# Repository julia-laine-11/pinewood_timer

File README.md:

# pinewood_timer
Timer system for a pinewood derby track. My grandma asked me to help her make one since her boy scout troop's track does not have one. I hope that I can make these more affordable so that her troop and other troops can get accurate timers that dont cost an arm and a leg.

*so whats in here?*
### [Hardware:](https://github.com/julia-laine-11/pinewood_timer/tree/main/Hardware)
* display_15_in
    - schematic
    - pcb
    - holds all the 7-segment displays and sensor receivers at the end of the track

* mainboard
    - schematic
    - pcb
    - holds the brains for the system
    - also where the power cable goes

### [Software:](https://github.com/julia-laine-11/pinewood_timer/blob/main/Software/code.md)
  - readme
* [Program](https://github.com/julia-laine-11/pinewood_timer/tree/main/Software/code/pinewood_program)
  - platformio project

### Overview
#### Overall Requirements
- easy operation -> plug and play
- 4 lanes
- time to the thousandths
- displays time in each lane
- displays placement in each lane
- cost less than $100-$120
    - 

##### Requirements per each lane
- start sensor - same trigger for all lanes
- stop sensor - seperate per each lane
- time display - 4 seven seg displays
- placement display - 1 larger seven seg display

##### Sensors
- Start sensor triggered by lever release
  - Microswitch is easy to install and get output from
  - I have to wait and see what my grandfather builds as the start mechanism
- Stop sensor - IR LED and IR Receiver
  - Sits in the middle of the groove the cars ride on underneath the finish line
  - Since it will likely be in a gym, the IR receiver should point down for less interference from the large lamps
  - A comparator or the STM ADC can be used if the voltage doesnt drop to an amount the STM recognizes as 0

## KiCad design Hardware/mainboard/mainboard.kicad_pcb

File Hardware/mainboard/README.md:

## mainboard

This board will be placed in a central location on the track. It connects to the power, reset button, start sensors, display at the end, and end sensors. A usb-c power supply will power it.

#### Current Board

9/30/25 - today i soldered the LED on. i got scared it wasnt working, but it turns out it was just a blue LED and therefore needed a smaller resistor. Then i plugged it in and i thought hte JTAG was backwards, but it turns out the decoup capacitors I placed are not in face decoupling and just capacitors. so i removed them and added a wire around them. im having issues connecting to the board. 

i got access to the board files from ece362, so i plan on comparing my layout to theirs to see what i did wrong. im disappointed but i think i can fix it (hopefully)

#### Current schematic
8/7/25 - fixed little silkscreen words. fixed DRC violations

### Old:

8/5/25 - i actually routed stuff today wohoo. i also added the design rules because i forgot to do that

not too much changed about the schematic:

i just added this for the start switch because i forgot about it

8/3/25 - added connectors and sheets

7/27/25 - organized and fixed power

7/26/25 - changed stm. added jtag. added usb for power. edited 3v3 supply. current schematic messy but its still in the works

Unfinished schematic

missing:
- connectors
- power in
- jtag
- usb - ttl

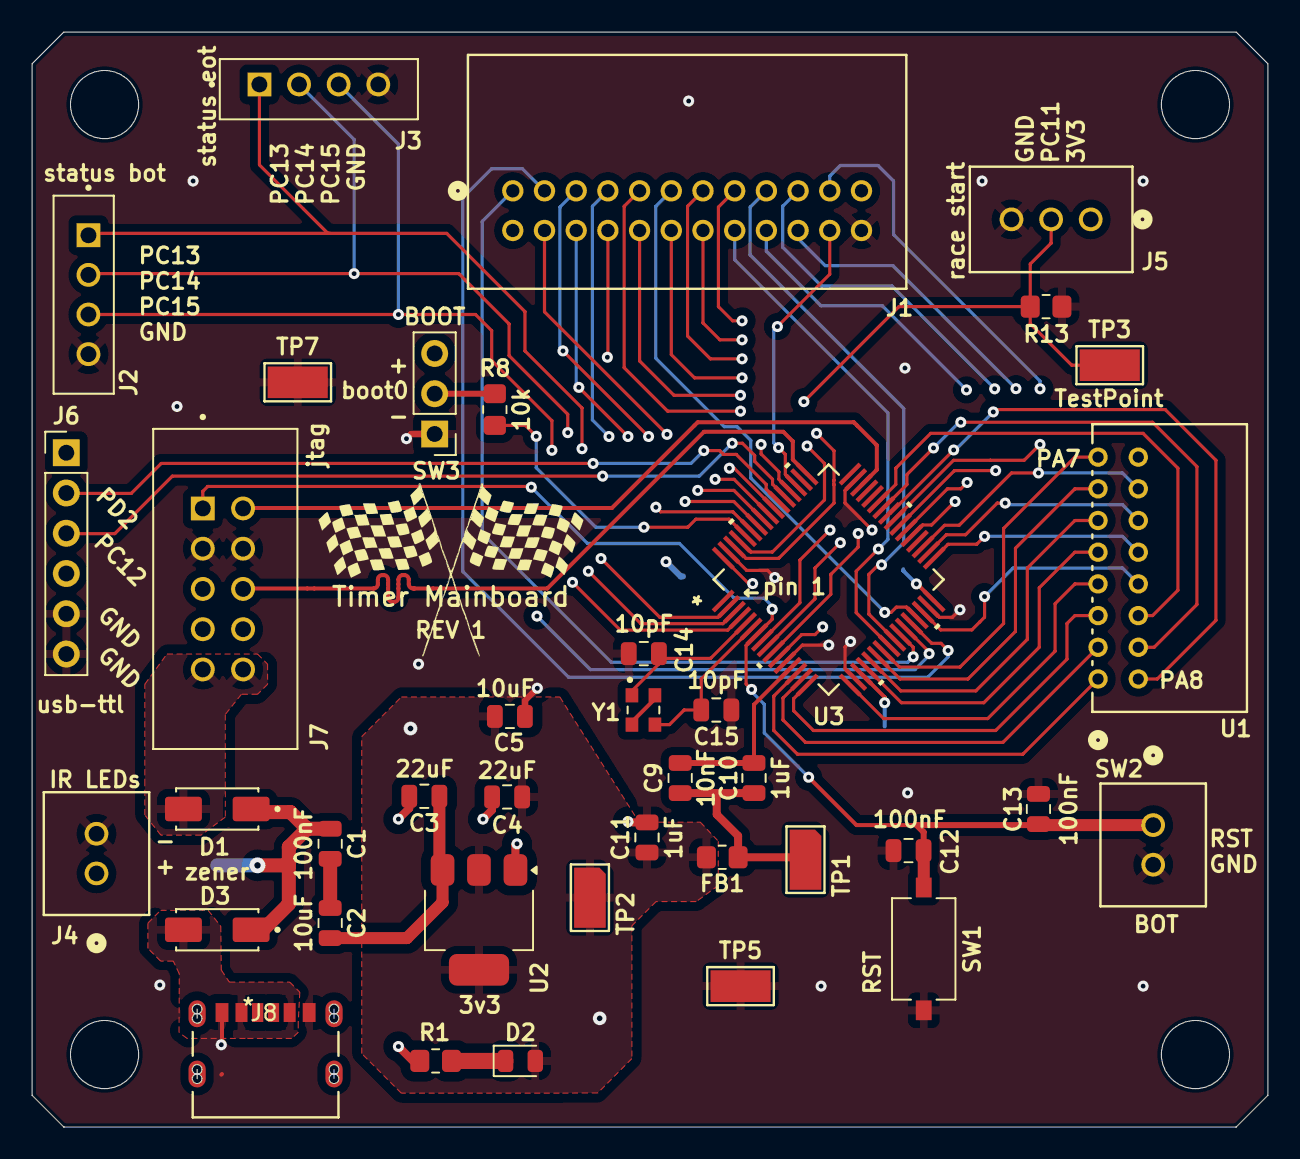
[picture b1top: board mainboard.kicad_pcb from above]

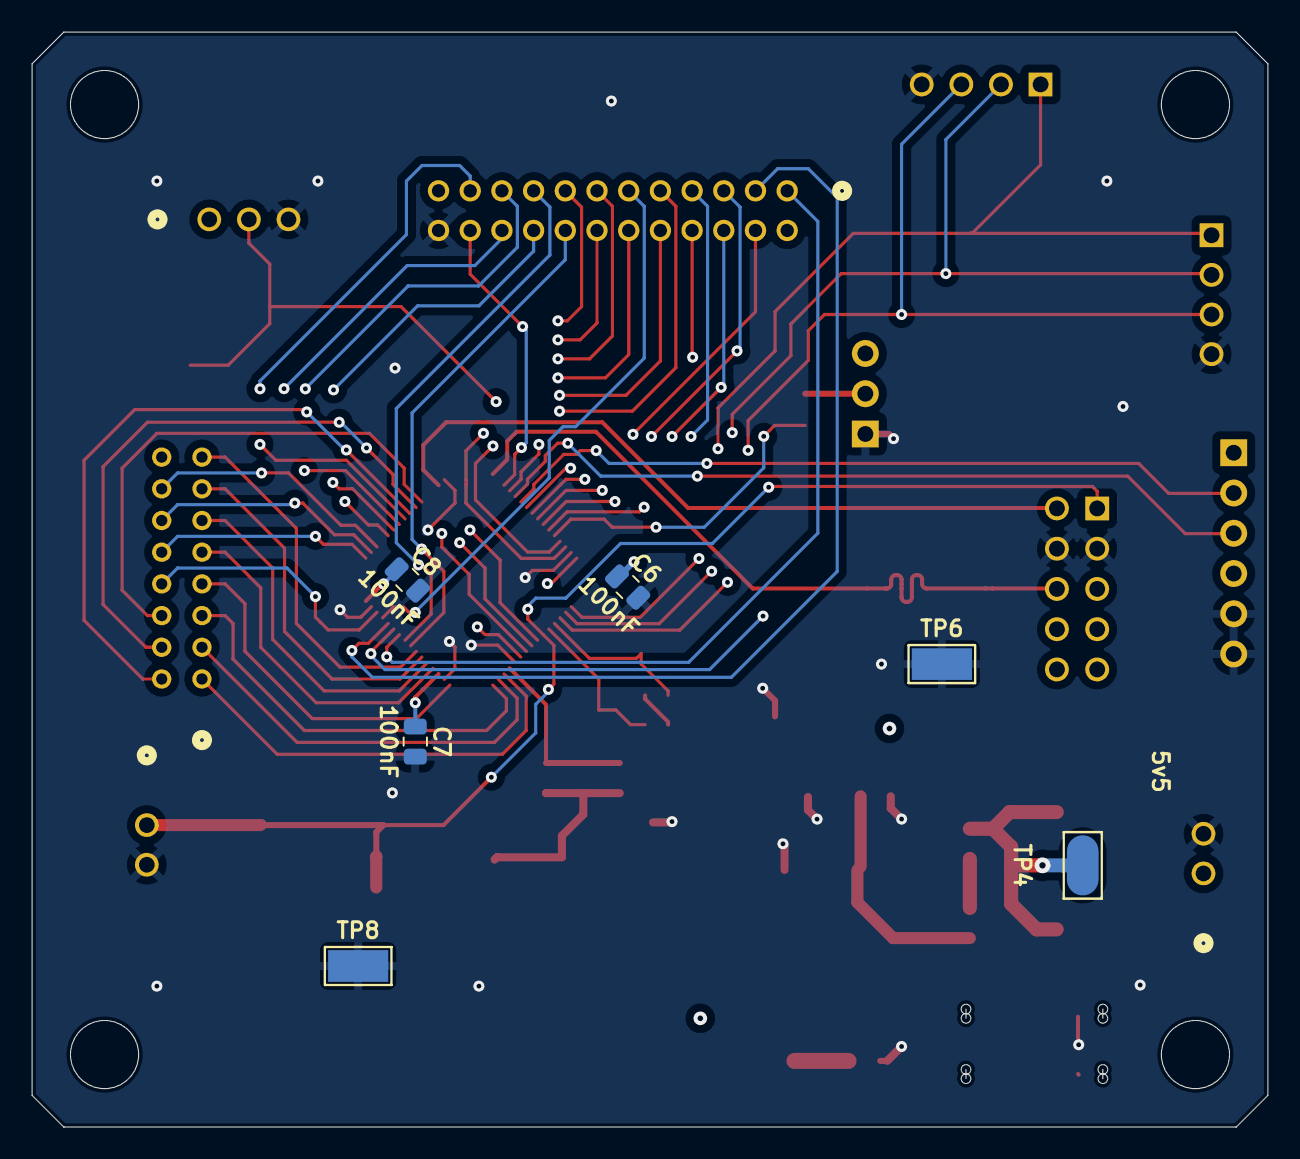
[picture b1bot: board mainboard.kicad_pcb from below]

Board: 4 copper layers, 78.0 x 69.1 mm, 49 parts (6 on the bottom side), 61 nets.

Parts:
C1, C6, C7, C8, C12, C13: 100nF; C_0805_2012Metric
C2, C5: 10uF; C_0805_2012Metric
C3, C4: 22uF; C_0805_2012Metric
C9: 10nF; C_0805_2012Metric
C10, C11: 1uF; C_0805_2012Metric
C14, C15: 10pF; C_0805_2012Metric
D1, D3: zener; DIOM5226X240N
D2: LED; D_0805_2012Metric
FB1: FerriteBead; R_0805_2012Metric_Pad1.20x1.40mm_HandSolder
H1, H2, H3, H4: MountingHole; MountingHole_4.3mm_M4_DIN965
J1: 559592430; CONN24_559592430_MOL
J2: status bot; 1x04_jst
J3: status eot; 1x04_jst
J4: B02B-XASK-1LFSN; 1X02_JST
J5: race start; 1X03_JST
J6: usb-ttl; PinHeader_1x06_P2.54mm_Vertical
J7: jtag; SULLINS_SBH11-PBPC-D05-ST-BK
J8: KUSBX-SMT-CS-6-BTR; 2171750001_MOL
R1: 1k5; R_0805_2012Metric_Pad1.20x1.40mm_HandSolder
R8: 10k; R_0805_2012Metric_Pad1.20x1.40mm_HandSolder
R13: R_US; R_0805_2012Metric_Pad1.20x1.40mm_HandSolder
SW1: ON-BOARD; SW_Tactile_SPST_NO_Straight_CK_PTS636Sx25SMTRLFS
SW2: BOT; CONN_B02B-XASK-1LFSN_JST
SW3: BOOT; PinHeader_1x03_P2.54mm_Vertical
TP1, TP2, TP3, TP4, TP5, TP6, TP7, TP8: TestPoint; TestPoint_Keystone_5019_Minature
U1: S16B-PHDSSLFSN; S16B-PHDSSLFSN_JST
U2: AMS1117-3.3; SOT-223-3_TabPin2
U3: STM32F091RCTx; STM32F091RCT6-M
Y1: Crystal_GND24; OSC_ECS-2520S25-250-FN-TR

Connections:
+3.3V: C4.1, C5.1, C6.1, C7.1, C8.1, C11.1, D2.2 (A), FB1.2, J1.23, J4.1, J5.1, SW3.3 (C), TP2.1, U2.2 (VO), U3.19 (VDD), U3.32 (VDD), U3.64 (VDD)
+3.3VA: C9.1, C10.1, FB1.1, TP1.1
/programming/3V3 REG DECOUP: C1.2, C2.1
/programming/3v3_reg_in: C2.2, C3.1, U2.3 (VI)
/programming/5v5_in_jtag: D1.2, J7.9, J7.10
/programming/5v5_post_diode: C1.1, D1.1, D3.1, TP4.1
/programming/5v5_usb: D3.2, J8.A9 (VBUS), J8.B9 (VBUS)
/programming/PWR_LED_CATHODE: D2.1 (K), R1.2
/stm/BOOT0: R8.2, U3.60 (PF11)
/stm/HSE_IN: C14.1, U3.5 (PF0), Y1.1
/stm/HSE_OUT: C15.1, U3.6 (PF1), Y1.3
/stm/SW_BOOT0: R8.1, SW3.2 (B)
GND: C3.2, C4.2, C5.2, C6.2, C7.2, C8.2, C11.2, C12.2, C13.2, C14.2, C15.2, J1.24, J2.4, J3.4, J4.2, J5.3, J6.5, J6.6, J7.3, J7.4, J8.A12 (GND), J8.B12 (GND), R1.1, R13.2, SW1.2 (B), SW2.2 (B), SW3.1 (A), TP5.1, TP6.1, TP7.1, TP8.1, U2.1 (GND), U3.12 (VSSA), U3.18 (VSS), U3.31 (VSS), U3.47 (VSS), U3.63 (VSS)
unnamed: C9.2, C10.2, U3.13 (VDDA)
unnamed: Y1.2, Y1.4
PA0: U1.1, U3.14 (PA0)
PA1: U1.2, U3.15 (PA1)
PA2: U1.3, U3.16 (PA2)
PA3: U1.4, U3.17 (PA3)
PA4: U1.5, U3.20 (PA4)
PA5: U1.6, U3.21 (PA5)
PA6: U1.7, U3.22 (PA6)
PA7: U1.8, U3.23 (PA7)
PA8: U1.9, U3.41 (PA8)
PA9: U1.10, U3.42 (PA9)
PA10: U1.11, U3.43 (PA10)
PB0: J1.1, U3.26 (PB0)
PB1: J1.2, U3.27 (PB1)
PB2: J1.3, U3.28 (PB2)
PB3: J1.4, U3.55 (PB3)
PB4: J1.5, U3.56 (PB4)
PB5: J1.6, U3.57 (PB5)
PB6: J1.7, U3.58 (PB6)
PB7: J1.8, U3.59 (PB7)
PB8: J1.9, U3.61 (PB8)
PB9: J1.10, U3.62 (PB9)
PB10: J1.11, U3.29 (PB10)
PB11: U1.12, U3.30 (PB11)
PB12: U1.13, U3.33 (PB12)
PB13: U1.14, U3.34 (PB13)
PB14: U1.15, U3.35 (PB14)
PC0: J1.12, U3.8 (PC0)
PC1: J1.13, U3.9 (PC1)
PC2: J1.14, U3.10 (PC2)
PC3: J1.15, U3.11 (PC3)
PC4: J1.16, U3.24 (PC4)
PC5: J1.17, U3.25 (PC5)
PC6: J1.18, U3.37 (PC6)
PC7: J1.19, U3.38 (PC7)
PC8: J1.20, U3.39 (PC8)
PC9: J1.21, U3.40 (PC9)
PC10: J1.22, U3.51 (PC10)
PC11: J5.2, R13.1, TP3.1, U3.52 (PC11)
PC12: J6.3, U3.53 (PC12)
PC13: J2.1, J3.1, U3.2 (PC13)
PC14: J2.2, J3.2, U3.3 (PC14)
PC15: J2.3, J3.3, U3.4 (PC15)
PD2: J6.2, U3.54 (PD2)
RST: C12.1, C13.1, J7.1, SW1.1 (A), SW2.1 (A), U3.7 (NRST)
SWCLK: J7.6, U3.49 (PA14)
SWDIO: J7.2, U3.46 (PA13)

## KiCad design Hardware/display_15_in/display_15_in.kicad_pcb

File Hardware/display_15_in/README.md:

## display_15_in
This was originally going to be a few seperate boards. I thought it would be easier and cheaper to make. 

It turns out to be cheaper to do it this way since the price of printing 3-4 boards per track and the price of 1 big one is the same. Also, with multiple boards you have to buy connectors and this 1 large board needs way less than 4 small ones.

This board connects to the main board with 1 8x2 connector and 1 12x2 connector.

### Parts
- LTS-3401LG - single 7-seg displays
- 4x TDCR1050M - quad 7-seg displays
- 20x PN2907A - cathode select bjt
- 20x 150 Ohm - mux to bjt
- 16x 47 Ohm - driver to display
- 2x 74HC138 - mux
- 2x TLC59211 - driver

#### pictures

>size comparison of digits 

#### schematics

#### PCB

Updated:

- still needs
  - power and ground traces
  - drill holes for mounting
  - test points

All traces routed (for now)

#### Log

7/12/25 - moved all of the components needed over to one project

7/13/25 - worked out connections between sheets and found connectors for mainboard. began layout (no traces)

7/19/25 - laying more traces and revising old ones. i am starting to hate the connector but i must use it

7/20/25 - sorted out the connector from hell. well, i at least made it better. i also discovered the "distribute evenly" and "align" functions

7/25/25 - finished traces, added test points

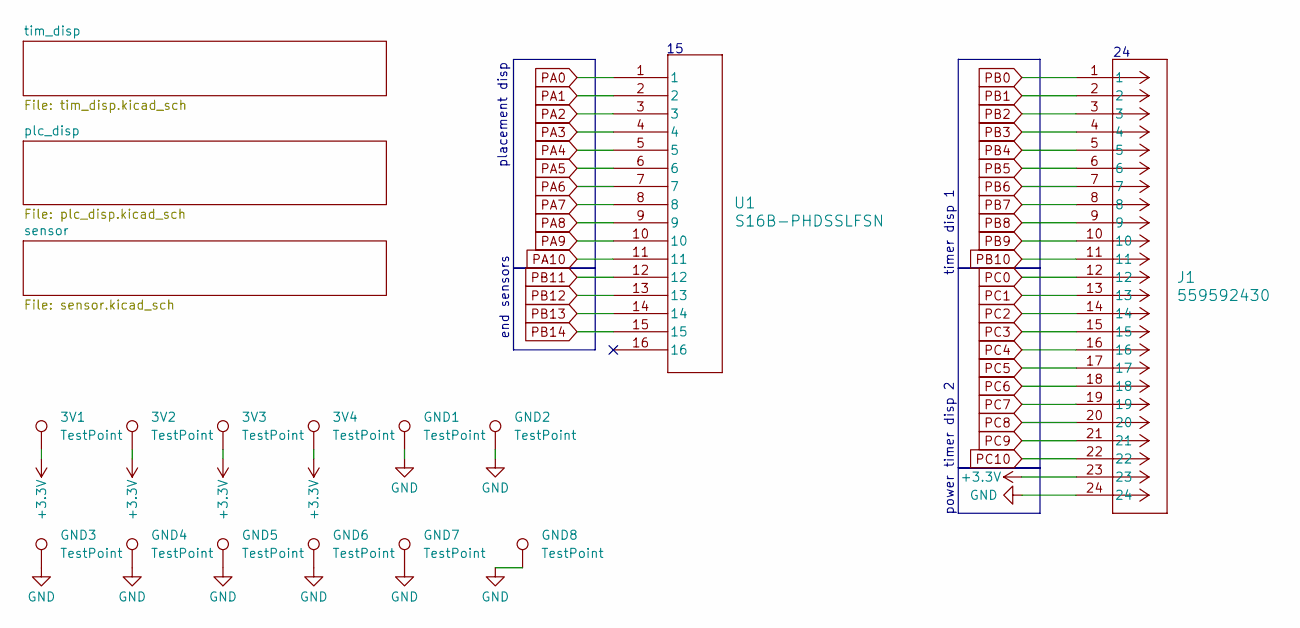
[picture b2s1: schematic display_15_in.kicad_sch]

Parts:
3V1, 3V2, 3V3, 3V4: TestPoint; TestPoint_Keystone_5019_Minature
GND1, GND2, GND3, GND4, GND5, GND6, GND7, GND8: TestPoint; TestPoint_Keystone_5019_Minature
J1: 559592430; CONN24_559592430_MOL
U1: S16B-PHDSSLFSN; S16B-PHDSSLFSN_JST

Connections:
+3.3V: 3V1.1, 3V2.1, 3V3.1, 3V4.1, J1.23; also elsewhere on the board
GND: GND1.1, GND2.1, GND3.1, GND4.1, GND5.1, GND6.1, GND7.1, GND8.1, J1.24; also elsewhere on the board
PA0: U1.1; also elsewhere on the board
PA1: U1.2; also elsewhere on the board
PA2: U1.3; also elsewhere on the board
PA3: U1.4; also elsewhere on the board
PA4: U1.5; also elsewhere on the board
PA5: U1.6; also elsewhere on the board
PA6: U1.7; also elsewhere on the board
PA7: U1.8; also elsewhere on the board
PA8: U1.9; also elsewhere on the board
PA9: U1.10; also elsewhere on the board
PA10: U1.11; also elsewhere on the board
PB0: J1.1; also elsewhere on the board
PB1: J1.2; also elsewhere on the board
PB2: J1.3; also elsewhere on the board
PB3: J1.4; also elsewhere on the board
PB4: J1.5; also elsewhere on the board
PB5: J1.6; also elsewhere on the board
PB6: J1.7; also elsewhere on the board
PB7: J1.8; also elsewhere on the board
PB8: J1.9; also elsewhere on the board
PB9: J1.10; also elsewhere on the board
PB10: J1.11; also elsewhere on the board
PC0: J1.12; also elsewhere on the board
PC1: J1.13; also elsewhere on the board
PC2: J1.14; also elsewhere on the board
PC3: J1.15; also elsewhere on the board
PC4: J1.16; also elsewhere on the board
PC5: J1.17; also elsewhere on the board
PC6: J1.18; also elsewhere on the board
PC7: J1.19; also elsewhere on the board
PC8: J1.20; also elsewhere on the board
PC9: J1.21; also elsewhere on the board
PC10: J1.22; also elsewhere on the board

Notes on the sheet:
power
timer disp 2
end sensors
placement disp
timer disp 1

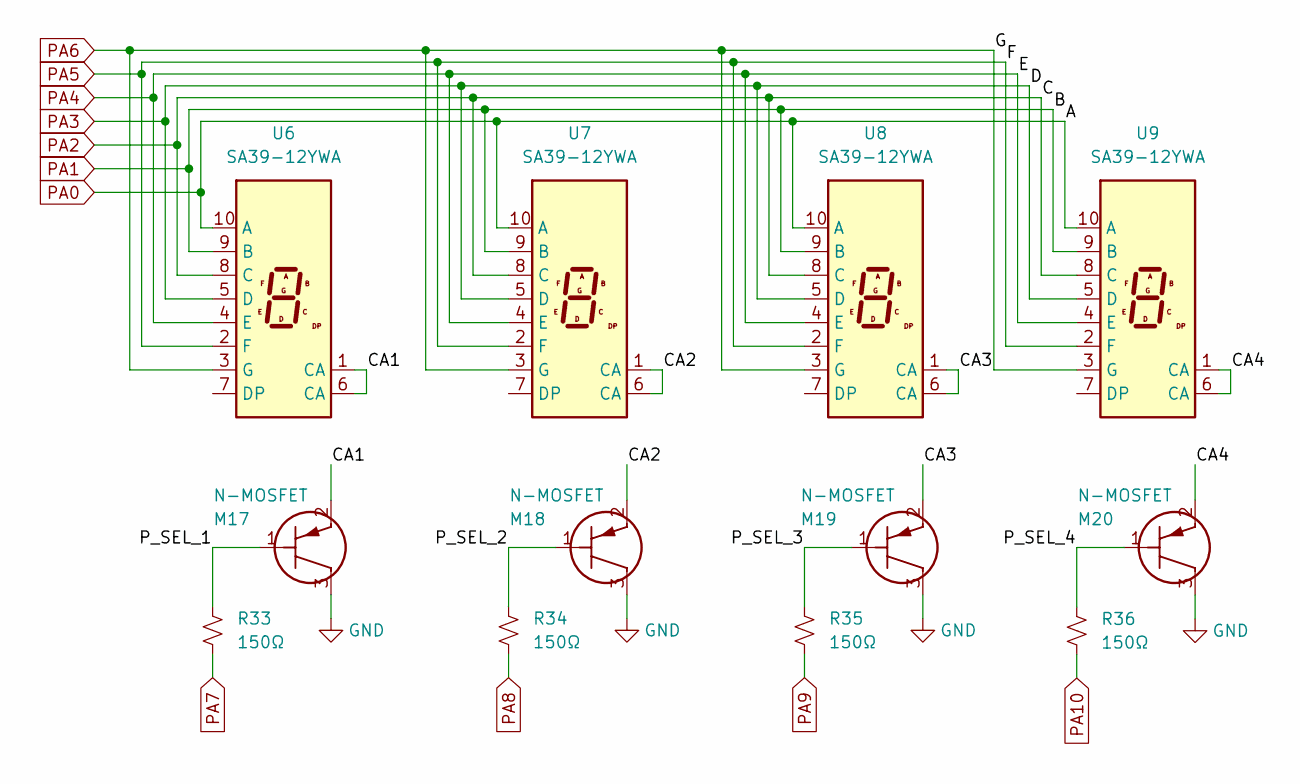
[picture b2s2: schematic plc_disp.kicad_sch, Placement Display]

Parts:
M17, M18, M19, M20: N-MOSFET; TO-236AB_SOT23_NEX
R33, R34, R35, R36: 150Ω; R_0805_2012Metric
U6, U7, U8, U9: SA39-12YWA; LDS-AA14RI

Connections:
/plc_disp/CA1: M17.2, U6.1 (CA), U6.6 (CA)
/plc_disp/CA2: M18.2, U7.1 (CA), U7.6 (CA)
/plc_disp/CA3: M19.2, U8.1 (CA), U8.6 (CA)
/plc_disp/CA4: M20.2, U9.1 (CA), U9.6 (CA)
/plc_disp/P_SEL_1: M17.1, R33.1
/plc_disp/P_SEL_2: M18.1, R34.1
/plc_disp/P_SEL_3: M19.1, R35.1
/plc_disp/P_SEL_4: M20.1, R36.1
GND: M17.3, M18.3, M19.3, M20.3; also elsewhere on the board
PA0: U6.10 (A), U7.10 (A), U8.10 (A), U9.10 (A); also elsewhere on the board
PA1: U6.9 (B), U7.9 (B), U8.9 (B), U9.9 (B); also elsewhere on the board
PA2: U6.8 (C), U7.8 (C), U8.8 (C), U9.8 (C); also elsewhere on the board
PA3: U6.5 (D), U7.5 (D), U8.5 (D), U9.5 (D); also elsewhere on the board
PA4: U6.4 (E), U7.4 (E), U8.4 (E), U9.4 (E); also elsewhere on the board
PA5: U6.2 (F), U7.2 (F), U8.2 (F), U9.2 (F); also elsewhere on the board
PA6: U6.3 (G), U7.3 (G), U8.3 (G), U9.3 (G); also elsewhere on the board
PA7: R33.2; also elsewhere on the board
PA8: R34.2; also elsewhere on the board
PA9: R35.2; also elsewhere on the board
PA10: R36.2; also elsewhere on the board

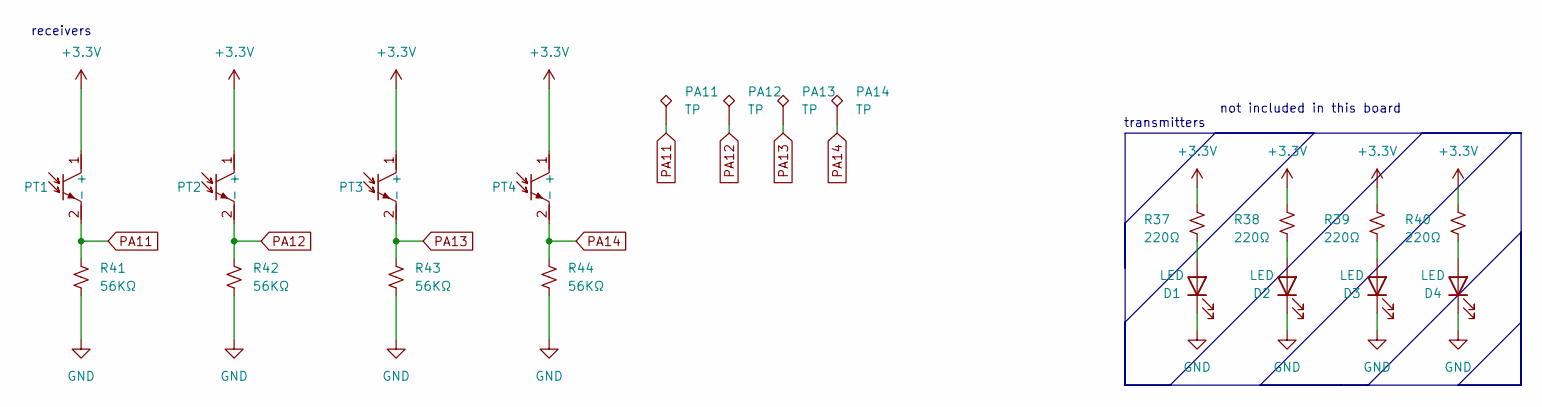
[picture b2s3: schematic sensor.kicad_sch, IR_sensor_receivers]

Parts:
D1, D2, D3, D4: LED; LED_D5.0mm
PA11, PA12, PA13, PA14: TP; TestPoint_Keystone_5019_Minature
PT1, PT2, PT3, PT4: LED_D5.0mm
R37, R38, R39, R40: 220Ω; R_0805_2012Metric
R41, R42, R43, R44: 56KΩ; R_0805_2012Metric

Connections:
+3.3V: PT1.1 (+), PT2.1 (+), PT3.1 (+), PT4.1 (+), R37.1, R38.1, R39.1, R40.1; also elsewhere on the board
GND: D1.1 (K), D2.1 (K), D3.1 (K), D4.1 (K), R41.2, R42.2, R43.2, R44.2; also elsewhere on the board
unnamed: D1.2 (A), R37.2
unnamed: D2.2 (A), R38.2
unnamed: D3.2 (A), R39.2
unnamed: D4.2 (A), R40.2

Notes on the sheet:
receivers
transmitters
not included in this board

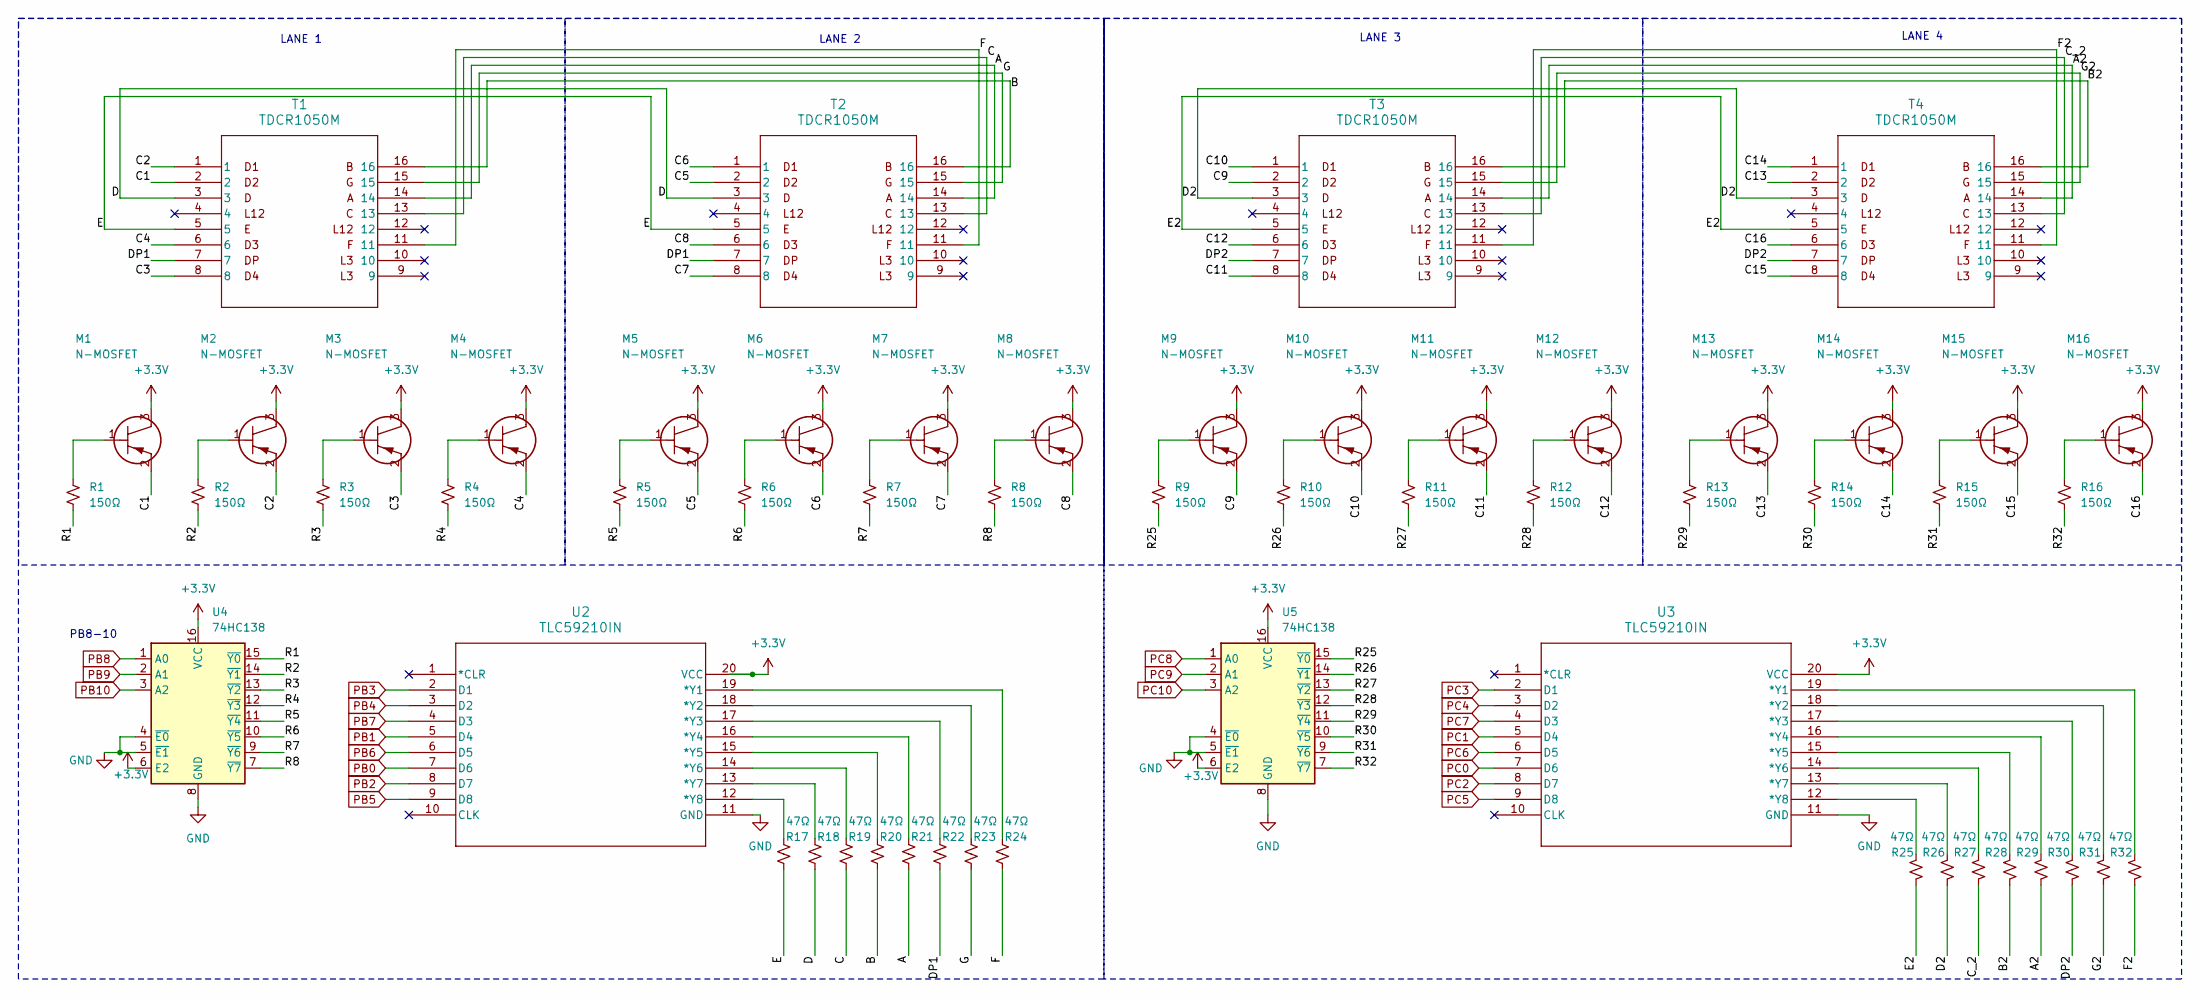
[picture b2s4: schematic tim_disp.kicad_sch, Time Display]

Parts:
M1, M2, M3, M4, M5, M6, M7, M8, M9, M10, M11, M12, M13, M14, M15, M16: N-MOSFET; TO-236AB_SOT23_NEX
R1, R2, R3, R4, R5, R6, R7, R8, R9, R10, R11, R12, R13, R14, R15, R16: 150Ω; R_0805_2012Metric
R17, R18, R19, R20, R21, R22, R23, R24, R25, R26, R27, R28, R29, R30, R31, R32: 47Ω; R_0805_2012Metric
T1, T2, T3, T4: TDCR1050M; TDCG1060M_VIS
U2, U3: TLC59210IN; SOP65P640X120-20N
U4, U5: 74HC138; SOIC127P600X175-16N

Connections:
+3.3V: M1.3, M2.3, M3.3, M4.3, M5.3, M6.3, M7.3, M8.3, M9.3, M10.3, M11.3, M12.3, M13.3, M14.3, M15.3, M16.3, U2.20 (VCC), U3.20 (VCC), U4.6 (E2), U4.16 (VCC), U5.6 (E2), U5.16 (VCC); also elsewhere on the board
/tim_disp/A: R21.2, T1.14, T2.14
/tim_disp/A2: R29.2, T3.14, T4.14
/tim_disp/B: R20.2, T1.16, T2.16
/tim_disp/B2: R28.2, T3.16, T4.16
/tim_disp/C: R19.2, T1.13, T2.13
/tim_disp/C1: M1.2, T1.2
/tim_disp/C2: M2.2, T1.1
/tim_disp/C3: M3.2, T1.8
/tim_disp/C4: M4.2, T1.6
/tim_disp/C5: M5.2, T2.2
/tim_disp/C6: M6.2, T2.1
/tim_disp/C7: M7.2, T2.8
/tim_disp/C8: M8.2, T2.6
/tim_disp/C9: M9.2, T3.2
/tim_disp/C10: M10.2, T3.1
/tim_disp/C11: M11.2, T3.8
/tim_disp/C12: M12.2, T3.6
/tim_disp/C13: M13.2, T4.2
/tim_disp/C14: M14.2, T4.1
/tim_disp/C15: M15.2, T4.8
/tim_disp/C16: M16.2, T4.6
/tim_disp/C_2: R27.2, T3.13, T4.13
/tim_disp/D: R18.2, T1.3, T2.3
/tim_disp/D2: R26.2, T3.3, T4.3
/tim_disp/DP1: R22.2, T1.7, T2.7
/tim_disp/DP2: R30.2, T3.7, T4.7
/tim_disp/E: R17.2, T1.5, T2.5
/tim_disp/E2: R25.2, T3.5, T4.5
/tim_disp/F: R24.2, T1.11, T2.11
/tim_disp/F2: R32.2, T3.11, T4.11
/tim_disp/G: R23.2, T1.15, T2.15
/tim_disp/G2: R31.2, T3.15, T4.15
/tim_disp/R1: R1.2, U4.15 (~Y0)
/tim_disp/R2: R2.2, U4.14 (~Y1)
/tim_disp/R3: R3.2, U4.13 (~Y2)
/tim_disp/R4: R4.2, U4.12 (~Y3)
/tim_disp/R5: R5.2, U4.11 (~Y4)
/tim_disp/R6: R6.2, U4.10 (~Y5)
/tim_disp/R7: R7.2, U4.9 (~Y6)
/tim_disp/R8: R8.2, U4.7 (~Y7)
/tim_disp/R25: R9.2, U5.15 (~Y0)
/tim_disp/R26: R10.2, U5.14 (~Y1)
/tim_disp/R27: R11.2, U5.13 (~Y2)
/tim_disp/R28: R12.2, U5.12 (~Y3)
/tim_disp/R29: R13.2, U5.11 (~Y4)
/tim_disp/R30: R14.2, U5.10 (~Y5)
/tim_disp/R31: R15.2, U5.9 (~Y6)
/tim_disp/R32: R16.2, U5.7 (~Y7)
GND: U2.11 (GND), U3.11 (GND), U4.4 (~E0), U4.5 (~E1), U4.8 (GND), U5.4 (~E0), U5.5 (~E1), U5.8 (GND); also elsewhere on the board
unnamed: M1.1, R1.1
unnamed: M2.1, R2.1
unnamed: M3.1, R3.1
unnamed: M4.1, R4.1
unnamed: M5.1, R5.1
unnamed: M6.1, R6.1
unnamed: M7.1, R7.1
unnamed: M8.1, R8.1
unnamed: M9.1, R9.1
unnamed: M10.1, R10.1
unnamed: M11.1, R11.1
unnamed: M12.1, R12.1
unnamed: M13.1, R13.1
unnamed: M14.1, R14.1
unnamed: M15.1, R15.1
unnamed: M16.1, R16.1
unnamed: R24.1, U2.19 (*Y1)
unnamed: R23.1, U2.18 (*Y2)
unnamed: R22.1, U2.17 (*Y3)
unnamed: R21.1, U2.16 (*Y4)
unnamed: R20.1, U2.15 (*Y5)
unnamed: R19.1, U2.14 (*Y6)
unnamed: R18.1, U2.13 (*Y7)
unnamed: R17.1, U2.12 (*Y8)
unnamed: R32.1, U3.19 (*Y1)
unnamed: R31.1, U3.18 (*Y2)
unnamed: R30.1, U3.17 (*Y3)
unnamed: R29.1, U3.16 (*Y4)
unnamed: R28.1, U3.15 (*Y5)
unnamed: R27.1, U3.14 (*Y6)
unnamed: R26.1, U3.13 (*Y7)
unnamed: R25.1, U3.12 (*Y8)
PB0: U2.7 (D6); also elsewhere on the board
PB1: U2.5 (D4); also elsewhere on the board
PB2: U2.8 (D7); also elsewhere on the board
PB3: U2.2 (D1); also elsewhere on the board
PB4: U2.3 (D2); also elsewhere on the board
PB5: U2.9 (D8); also elsewhere on the board
PB6: U2.6 (D5); also elsewhere on the board
PB7: U2.4 (D3); also elsewhere on the board
PB8: U4.1 (A0); also elsewhere on the board
PB9: U4.2 (A1); also elsewhere on the board
PB10: U4.3 (A2); also elsewhere on the board
PC0: U3.7 (D6); also elsewhere on the board
PC1: U3.5 (D4); also elsewhere on the board
PC2: U3.8 (D7); also elsewhere on the board
PC3: U3.2 (D1); also elsewhere on the board
PC4: U3.3 (D2); also elsewhere on the board
PC5: U3.9 (D8); also elsewhere on the board
PC6: U3.6 (D5); also elsewhere on the board
PC7: U3.4 (D3); also elsewhere on the board
PC8: U5.1 (A0); also elsewhere on the board
PC9: U5.2 (A1); also elsewhere on the board
PC10: U5.3 (A2); also elsewhere on the board

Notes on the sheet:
LANE 4
LANE 2
PB8-10
LANE 1
LANE 3

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
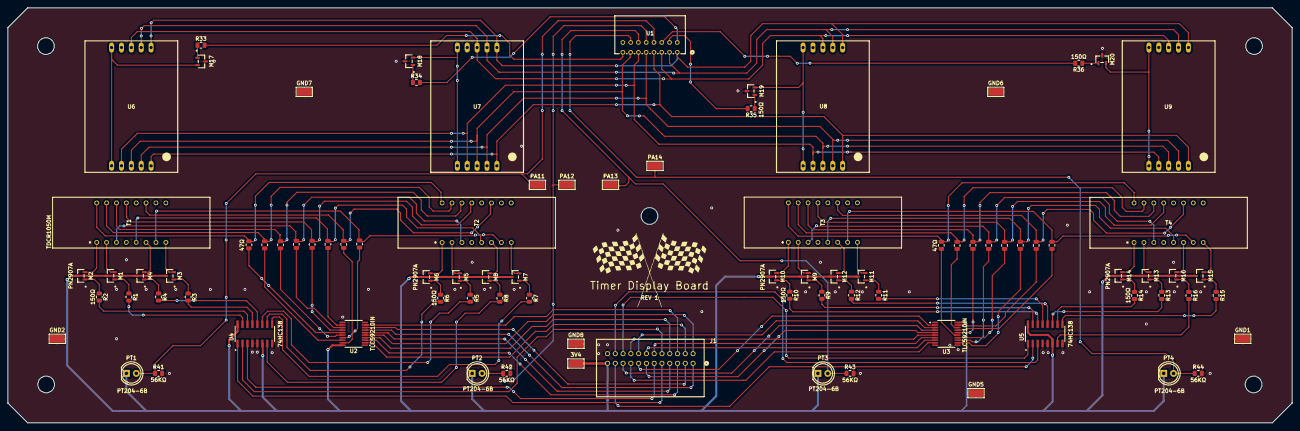
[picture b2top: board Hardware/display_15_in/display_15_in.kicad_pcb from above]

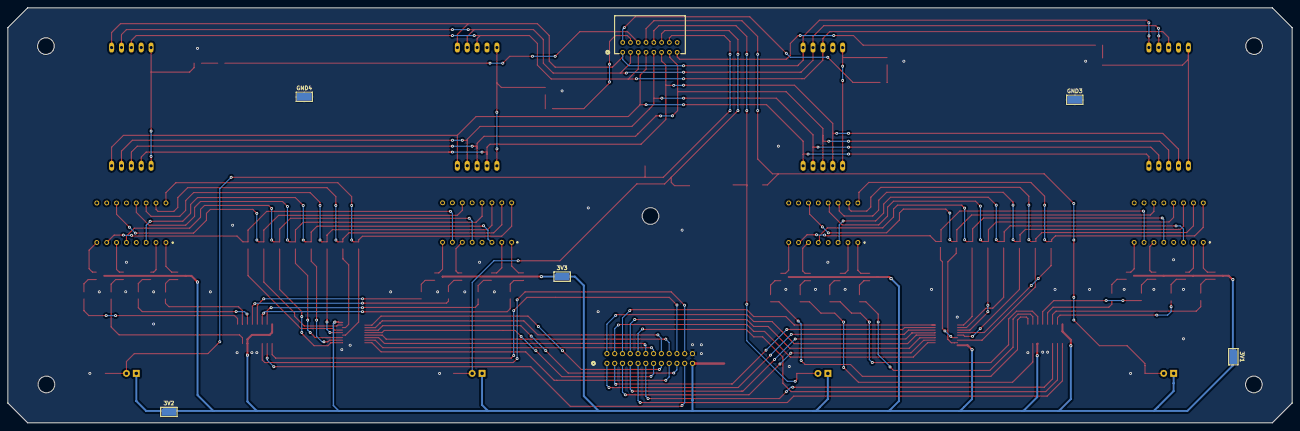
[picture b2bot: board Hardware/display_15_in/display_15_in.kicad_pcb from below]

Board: 2 copper layers, 330.2 x 106.7 mm, 94 parts (5 on the bottom side), 127 nets.

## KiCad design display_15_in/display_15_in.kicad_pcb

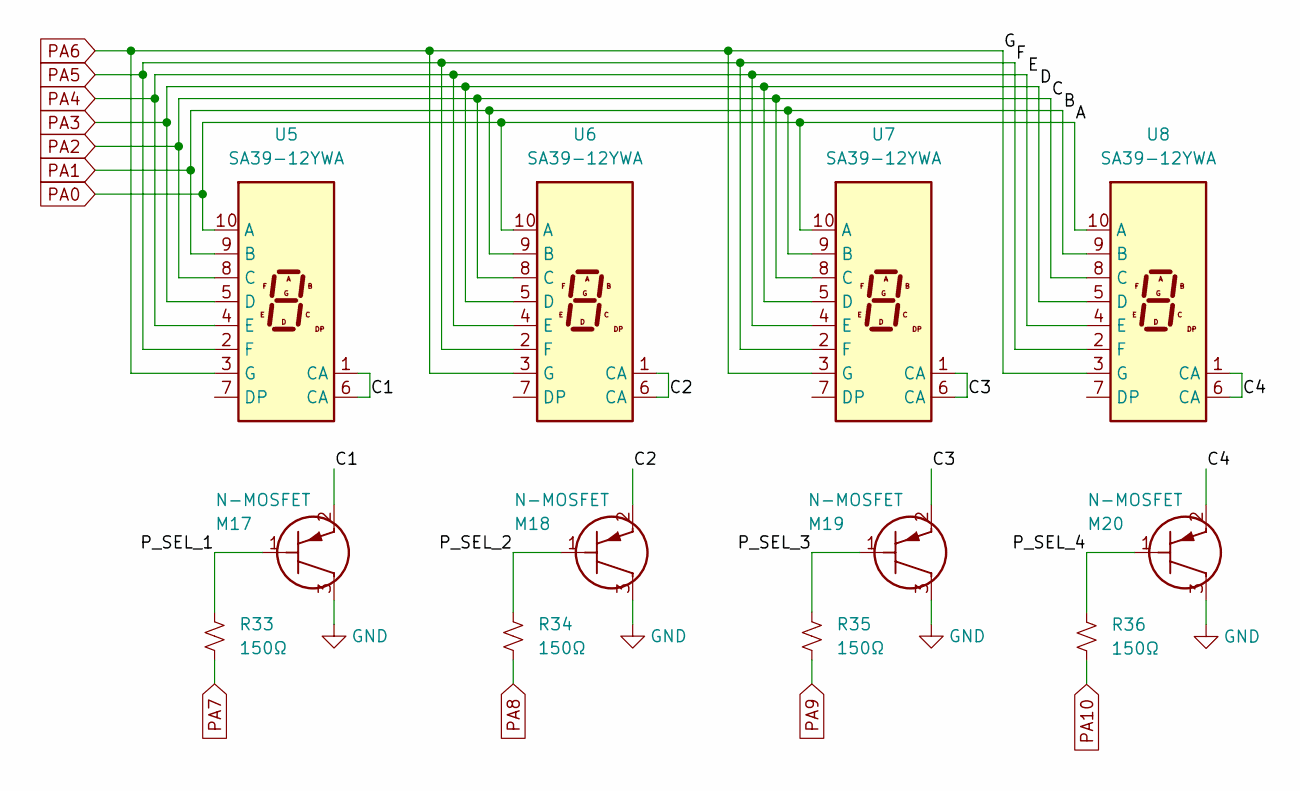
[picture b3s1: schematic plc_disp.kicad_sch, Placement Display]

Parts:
M17, M18, M19, M20: N-MOSFET; TO-236AB_SOT23_NEX
R33, R34, R35, R36: 150Ω; R_0805_2012Metric
U5, U6, U7, U8: SA39-12YWA; LDS-AA14RI

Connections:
/plc_disp/C1: M17.2, U5.1 (CA), U5.6 (CA)
/plc_disp/C2: M18.2, U6.1 (CA), U6.6 (CA)
/plc_disp/C3: M19.2, U7.1 (CA), U7.6 (CA)
/plc_disp/C4: M20.2, U8.1 (CA), U8.6 (CA)
/plc_disp/P_SEL_1: M17.1, R33.1
/plc_disp/P_SEL_2: M18.1, R34.1
/plc_disp/P_SEL_3: M19.1, R35.1
/plc_disp/P_SEL_4: M20.1, R36.1
GND: M17.3, M18.3, M19.3, M20.3; also elsewhere on the board
PA0: U5.10 (A), U6.10 (A), U7.10 (A), U8.10 (A); also elsewhere on the board
PA1: U5.9 (B), U6.9 (B), U7.9 (B), U8.9 (B); also elsewhere on the board
PA2: U5.8 (C), U6.8 (C), U7.8 (C), U8.8 (C); also elsewhere on the board
PA3: U5.5 (D), U6.5 (D), U7.5 (D), U8.5 (D); also elsewhere on the board
PA4: U5.4 (E), U6.4 (E), U7.4 (E), U8.4 (E); also elsewhere on the board
PA5: U5.2 (F), U6.2 (F), U7.2 (F), U8.2 (F); also elsewhere on the board
PA6: U5.3 (G), U6.3 (G), U7.3 (G), U8.3 (G); also elsewhere on the board
PA7: R33.2; also elsewhere on the board
PA8: R34.2; also elsewhere on the board
PA9: R35.2; also elsewhere on the board
PA10: R36.2; also elsewhere on the board
